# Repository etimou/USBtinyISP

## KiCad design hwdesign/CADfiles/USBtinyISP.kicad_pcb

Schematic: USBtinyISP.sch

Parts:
C1: 0.1u
C2, C3: 27p
D1, D2: 3.3
D3, D4: LED
IC1: ATTINY2313A-P; DIP20
J1: USB_A_MALE
P1, P2, P3, P4, P5, P6: CONN_1
P7, P8: CONN_2
R1: 10k
R2, R3, R6, R7, R8: 1.5k
R4, R5: 68
X1: 12MHz

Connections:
/MISO: IC1.18 ((PCINT6/MISO/DO)PB6), P1.1
/MOSI: P4.1, R2.2
/RST: IC1.16 ((PCINT4/OC1B)PB4), P5.1, P7.2 (PM)
/SCK: P3.1, R3.2
GND: C1.2, C2.2, C3.2, D1.1 (A), D2.1 (A), D3.2 (K), D4.2 (K), IC1.10 (GND), J1.4, P6.1
unnamed: D1.2 (K), J1.3, R4.2
unnamed: D2.2 (K), J1.2, R5.2, R6.1
unnamed: IC1.6 ((PCINT13/CKOUT/XCK/INT0)PD2), R4.1
unnamed: IC1.17 ((PCINT5/MOSI/DI/SDA)PB5), R2.1
unnamed: IC1.19 ((PCINT7/USCK/SCK/SCL)PB7), R3.1
unnamed: C2.1, IC1.5 (PA0(XTAL1/CLKI/PCINT8)), X1.2
unnamed: IC1.12 ((PCINT0/AIN0)PB0), R7.1
unnamed: IC1.7 ((PCINT14/INT1)PD3), R5.1
unnamed: IC1.1 (PA2(~RESET~/dW/PCINT10)), P7.1, R1.2
unnamed: D3.1 (A), R7.2
unnamed: D4.1 (A), R8.2
unnamed: IC1.9 ((PCINT16/OC0B/T1)PD5), R8.1
unnamed: P2.1, P8.2 (PM)
unnamed: C3.1, IC1.4 (PA1(XTAL2/PCINT9)), X1.1
VCC: C1.1, IC1.20 (VCC), J1.1, P8.1, R1.1, R6.2

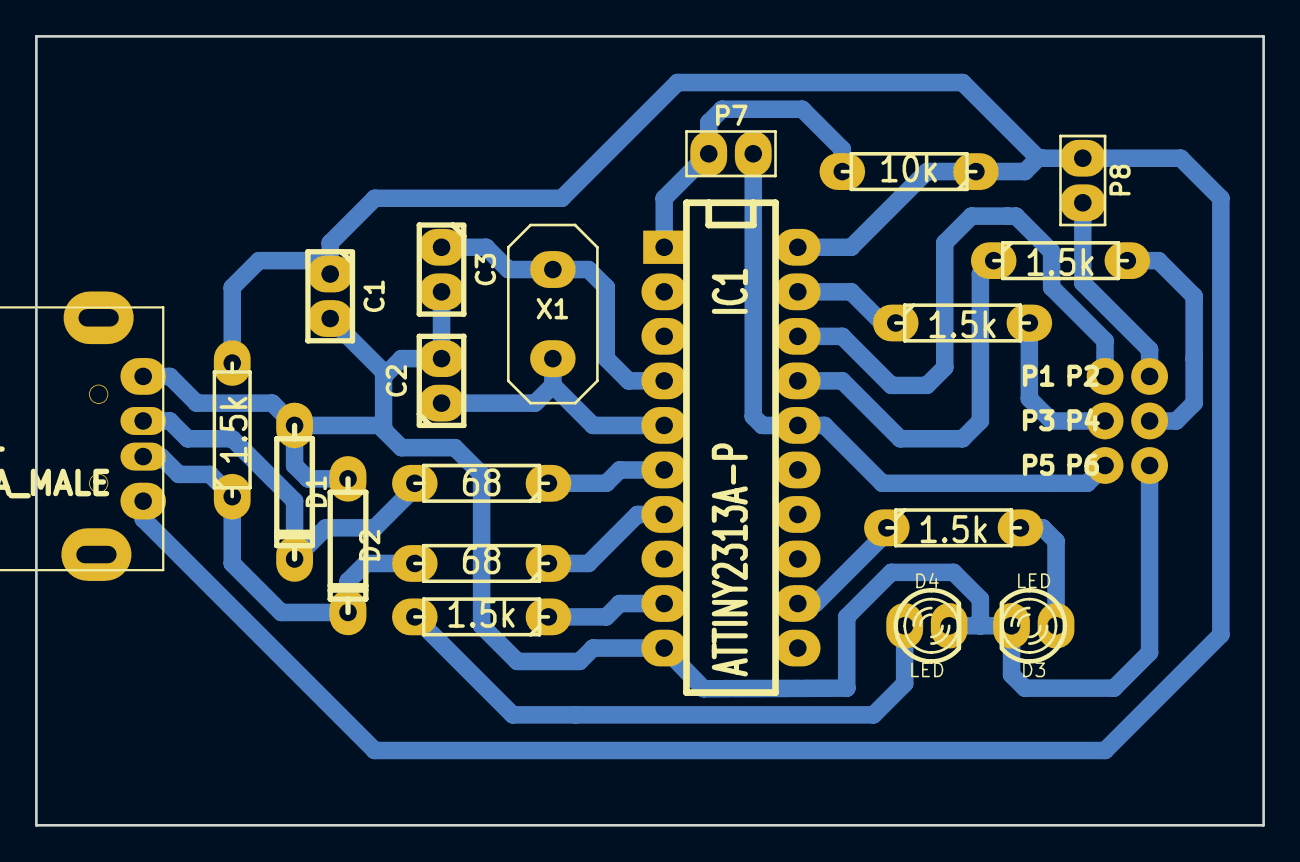
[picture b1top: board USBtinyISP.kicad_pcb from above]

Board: 2 copper layers, 70.0 x 45.0 mm, 26 parts (0 on the bottom side), 20 nets.

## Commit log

2013-12-15 initial version
2013-12-15 add sourcecode from adafruit
